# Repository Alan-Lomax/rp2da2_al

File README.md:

# rp2da2

Model Railway Distributed Automation for RP2 (and other MicropPython MCUs).

---

## Hardware and Environment

The primary target Micro Controller Units for this project are Raspberry Pi RP2
based and run MicroPython V1.26 or later. Testing has principly taken place on
Pico, Pico W, Pico 2W and Arduino Nano RP2040 Connect platforms.
DCC and RailCom components use the RP2 Programmable IO peripheral so must be run
on an RP2040 or RP2350 based MCU.
Other application components
may run on other MicroPython capabable platforms with no, or minor modifications.

Primary components are:

- a command station with integrated booster/RailCom cutout and global RailCom detector
- a local RailCom detector module with up to four detectors and current based occupancy detection.

A booster is required to convert the DCC signal into a form suitable for
suppling power directly to track. The reference booster is the Texas
Instruments DRV8874 mounted on a Pololu header. This also acts as the RailCom cutout. This may deliver up to 2.9 A
instantaniously but is only rated for 2.1 A continuous load. You will also
need a suitable DC power supply.

RailCom detectors have been specifically designed for this project with circuit
schematics and PCB designs for both command station and local detectors. The PCB designs
and applications have been designed around a standard set of GPIO pin
allocations. The local RailCom detector also provides a block occupancy indication using
conventional current flow detection. This triggers at a nominal 1 mA enabling detection of 10 kΩ wheel set resistors.
SPI1 and other GPIO pins not currently used by the application suite
may be exposed PCB on headers.

### GPIO Pins, I2C & SPI

On the command station one global detector is
available for the receipt of Channel 2 datagrams. Pin allocations for a Pico based command station are as follows.
Pin allocations on other platforms may differ.

|GPIO Pin (Pico & Nano)|Function|
|---|---|
|4|OLED I2C0:sda|
|5|OLED I2C0:scl|
|16|RailCom Ch 2 rx|
|18|DRV8874 EN|
|19|DRV8874 nSleep|
|20|DRV8874 PH|
|21|DRV8874 nFault|
|22|NeoPixel chain (2 LEDs)|
|26|DRV8874 Current Sense|
|Ground|DRV8874 iMode|
|Ground|DRV8874 pMode|
|NC|DRV8874 Vref|
|22|NeoPixel chain (2 LEDs)|

The following table shows pin allocations for a four block local detector on a Pico series
platform. Pin allocations on other platforms may differ. Other platforms may be able to
support additional local detectors.

I2C0, I2C1 and SPI1 pin assignments follow the MicroPython default pin assignments for
these peripherals.

SPI1 may be wired to a PCB header for off board connection.

I2C1 is used to support conventional current based detector functions.
It may be wired to a PCB header for off board connection too.

|GPIO Pin|Pico / Pico W|
|---|---|
|4|OLED I2C0:sda|
|5|OLED I2C0:scl|
|6|I2C1:sda|
|7|I2C1:scl|
|8|SPI1 MISO|
|9|SPI1 CS(primary)|
|10|SPI1 SCK|
|11|SPI1 MOSI|
|12|SPI1 additional GPIO (e.g. interrupt)|
|13|SPI1 CS(alternative)|
|14|RailCom ch 1 (a) rx|
|15|RailCom ch 1 (a) orientation|
|16|RailCom ch 1 (b) rx|
|17|RailCom ch 1 (b) orientation|
|18|RailCom ch 1 (c) rx|
|19|RailCom ch 1 (c) orientation|
|20|RailCom ch 1 (d) rx|
|21|RailCom ch 1 (d) orientation|
|22|NeoPixel chain (5 LEDs)|
|26|User press button|
|27|RailCom cutout detect|

### Programmable Input/Output & State Machines

The DCC and RailCom components make extensive use of the RP2 Programmable
Input/Output (PIO) peripherals. Each PIO peripheral has four State Machines.
On the Pico W and Pico2 W use of the radio module also requires use of a PIO
State Machine and a State Machine may also be used to drive a NeoPixel chain.
The RP2040 has 2 PIO peripherals and the RP2350 has 3.  MicroPython numbers
the State Machines on these as 0 to 7 and 0 to 11 respectively.

Note that the tables show the default radio state
machines as grabbed if available by the MicroPython
Wi-Fi module/RP SDK library.
The MicroPython application code leaves these
free for the radio rather than specifically
allocating them.

#### Command Station/Global Detector

|State Machine|Function|
|---|---|
|0|DCC generation|
|1 - 3|Not available. DCC generation uses virtually all PIO 0 memory|
|4|Radio on Pico W|
|5|NeoPixel on Pico / Pico W|
|6|RailCom Channel 2 timing|
|7|RailCom Channel 2 RX|
|8|Radio on Pico2 W|
|9|NeoPixel on Pico2 / Pico2 W|

#### Local Detector

|State Machine|Function|
|---|---|
|0|Block A RailCom Channel 1 timing|
|1|Block A RailCom RX|
|2|Block B RailCom Channel 1 timing|
|3|Block B RailCom RX|
|4|Block C RailCom Channel 1 timing|
|5|Block C RailCom RX|
|6|Block D RailCom Channel 1 timing|
|7|Block D RailCom RX|
|8|Radio on Pico2 W|
|9|NeoPixel on Pico2 / Pico2 W|

## Software Modules

### Utility & UI

**device** - This provides the Device class, a base class for hardware device
drivers and similar objects.

**oled0_91** - Module for 0.91 inch OLED on i2c0

**led** - Module to drive ws2812 LEDs or similar.  A string of up to five LEDs is supported.
The first LED displays the backend communications state. Additional LEDs display the
command station track status or local block status as appropriate.

**screen** - This is the screen application module. It specifies the Screen class.

### Communications

**mqtt_client** - This provides a simple MQTT client. Use of MQTT requires an MQTT broker. E.g Mosquitto. There are ports
of this for Windows, MAC/OS, and Linux (e.g. Ubuntu, Raspberry Pi OS).

**mqtt\*** - Other MQTT modules provide interfaces for MQTT devices and agents.
These may be used with JMRI but JMRI MQTT specifications will need to be
changed from the default. Initially we support cabs, power and blocks.
Blocks include occupancy sensor and RailCom reporter.

**wifi** - This acts as wrapper for the standard MicroPython network/Wi-Fi functions.

### DCC and RailCom

These modules are dependent on RP2 series processor programable input/output peripherals (PIO)
for DCC command serialisation and RailCom response processing.

#### Command Station Modules

**dcc_command** - This module provides high level APIs. It and associated modules contain
the functions and classes for DCC command station.

**dcc_cmd_util** - This module contains classes for DCC command objects.

**dcc_cmd_pio** - This module contains the class and functions for low level
DCC Command Serialisation for use with RailCom detection.

**dcc_rc_ch2** - This module contains the functions and classes for DCC RailCom
command station global detector mobile responses on Channel 2.

**trk_mon** - This module monitors the booster and track status by looking at the DRV8874
sleep, enable, fault and current sense pins.

#### Local RailCom Detector Modules

**dcc_rc_ch1** - This module contains the functions and classes for DCC RailCom
block detection on Channel 1.

**blk_mon** - This module contains classes for block occupancy detection based on current
consumption. It works in parallel with the RailCom Channel 1 detector.

#### Common Module

**dcc_rc_pio**  - This module contains the functions and classes for low level
RailCom datagram reading. It's applicable for block occupancy detection on
Channel 1 and central dcc command decoder responses on Channel 2.

---

## Configuration

Configuration files hold information required at runtime.  The files use the JSON format.
They are held in the repository's conf directory. They must be copied to a top level directory on the
target machine called conf. The configuration files in the repository should be taken as examples.
They need to be modified outside the repository to reflect local requirements. The Thonny editor
may be used to update them as required once they have been copied to the target machine.

### Wi-Fi

The config file specifies:

- Network country code
- SSID - your Wi-Fi network name
- password - the network password
- host name - the name to be used by local machine. This needs to be changed
from the MicroPython default to avoid duplicates.

```json
{"country": "myCountry", "password": "myPassword", "ssid": "mySSID", "hostname":"myHostName"}
```

### MQTT

***Pico Configuration***

The config file specifies:

- the MQTT broker's host name
- the local machine client ID.  The client id is required as by default Mosquitto will not permit access without it. However if not specified here the client id will be set to the network host name.
- port - the MQTT port number. By default this is set to 1883 and this setting may be ommitted.

```json
{"broker": "myBroker", "clientId": "myClientName", "port": 1883}
```

On the command station the MQTT connection supports track power and cabs.
On the local detector the MQTT connection supports sensor updates and reporters.
The MQTT connection may be used to communicate with JMRI.
Generally topics match those used by JMRI but some modifications are required to JMRI defaults
as configured on the MQTT connections settings.

***Mosquitto Configuration***

The Mosquitto configuration file is held in mosquitto.conf. The location of the file is OS dependent.
For Raspberry Pi OS it's

```text
/etc/mosquitto/mosquitto.conf
```

A couple of lines may need to be added.

```text
allow_anonymous true

listener 1883
```

Note that connections to Mosquitto will not be authenticated. Do not do this unless inward connections to your network are blocked (or you don't mind aliens hacking your model railway).

***JMRI MQTT Configuration***

  Check 'Additional Connection Settings' under
Preferences->Connections for the MQTT connection to access the JMRI MQTT configuration.

|Setting|Value|
|---|---|
|Sensor send topic:|track/sensor/{0}/set|
|Sensor receive topic:|track/sensor/{0}/event|
|Power send topic:|track/power/set|
|Power receive topic:|track/power/event|

---

## Software Installation

### General

Copy the python (.py) files from the lib and rp2dcc directories to the Pico using Thonny or similar.
Don’t replicate the repository directory structure. Copy the files from both directories to the
lib directory at the Pico files system top level.
Note that MicroPython will only search the top level directory and the lib directory for
*.py files.
Don’t bother with the \_\_init\_\_.py  files.
These are purely documentary at the moment.
Also ignore the test directory.

The screen driver will object if it can’t find the OLED on the i2c bus.
Most 0.91" OLEDs include i2c pull-ups so these should not be needed.

Copy the files from the conf directory to a directory on the Pico named conf.  Edit the configuration files
**after copying**.

### Command Station

The main.py in the examples/command directory is a command station version. It provides MQTT connectivity
allowing the command station to be controlled from JMRI or similar.
Copy this main.py from the command directory to the top level directory on the target device.
Alternatively there is a test harness test_dcccmd.py in the test directory.
This may be run using Thonny. Load this into the Thonny editor window and ‘Run current script’
(green play button). It will auto-detect whether on a RP Pico or
Arduino Nano RP2040 Connect and allocate the detector pins accordingly.
It creates the DCCCommand object (named dcc).

If OK you will get an invitation to type at the REPL, but the program will still be
running in the background. The OLED display shows a ’splash’.

You can enter DCC API commands at the REPL preceded by
'dcc.'. E.g.:

```py
>>> dcc.power(1)
```

### Block Detector

The main.py scripts in the dual\_, and quad\_ local_detect directories are the block detector versions. They
monitor two and four blocks respectively.

They provide MQTT connectivity
allowing the block detector to report to JMRI or similar.
Copy the main.py from the dual or quad directory to the top level directory on the target device.

Alternatively there are test harnesses in the test directory.

***test_dccrc1.py*** runs the local RailCom detectors.

***test_quad_blk.py*** runs the current based occupancy Train detectors.

Both may be run using Thonny. Load the program into the Thonny editor window and ‘Run current script’
(green play button). The program will auto-detect whether on a RP Pico or
Arduino Nano RP2040 Connect and allocate the detector pins accordingly.
It creates the channel 1 block detector objects or current based detector for the blocks.

The program will run forever.

Block occupancy details will be displayed on the OLED screen. Press the user button to see RailCom stats.

---

## DCC API

### Module dcc_command

---
class **DCCCommand** *(DCC_pn, sleep_pn, gen_sm_num, enable_pn)*

Parameters

- *DCC_pn* Pin number allocated for DCC output.

- *sleep_pn* Pin number allocated to the booster for powering the track

- *gen_sm_num* PIO state machine number to be used for DCC Generation

- *enable_pn* Pin number to enable the DRV8874.

---

method **power** *(p=None)*

DCC Power On/Off

Start and stop command packet transmission scheduling.

Changing the power state will cause the new power state available flag to be set.

Parameters

- *p* 1 for power on, 0 for power off, None for get power status

Returns

- power status as held by the DCC generator.

---

method **read_cv** *(address, cv_num)*

This initiates reading a CV using Programming on Main in conjunction with RailCom.
The command is validated and the read request scheduled for action. The addressed decoder must be
active and the command will be rejected by the command generator class this is not true.

The CV value will be displayed on the OLED.

Parameters

- *address*

- *cv_num* cv number as entered - users count from 1, DCC counts from 0!

---

method **write_cv** *(address, cv_num, new_val)*

This initiates writing a CV using Programming on Main in conjunction with RailCom.

The command is validated and the write request scheduled for action. The addressed
decoder must be active and the command will be rejected by the command generator class
this is not true.

The updated CV value will be displayed on the OLED if the write is successful.

Parameters

- *address*

- *cv_num* cv number as entered - users count from 1, DCC counts from 0!

- *new_val* the new value for the CV

---

method **set_fg1** *(address, f_num, state)*

Set Function Group 1

This sets or clears a function in group 1. The forward light is usually function number 0.

See NMRA S-9.2.1 Section 2.3.4

Parameters

- *address* the address of the decoder - may be short or long

- *f_num* function number to set or clear

- *state* 1 for set, 0 for clear

Returns

- True if validation is passed and the packet is scheduled for transmission. False if validation fails.

---

method **set_speed** *(address, dir, speed)*

Set Speed.

This sets the direction and speed. Direction may be forward or reverse.

The packet generated will be for a 128 step speed setting and decoders must be configured for
28/128 speed steps.

See NMRA S-9.2.1 Section 2.3.2.1

Parameters

- *address* the address of the decoder - may be short or long

- *direction* 1 for forward, -1 for reverse

- *speed* the speed to be set - range 0 to 127

Returns

- True if validation is passed and the packet is scheduled for transmission. False if validation fails.

---

method **wait_for_flag** *()*

Wait for the new state available flag.

The new state available flag is an instance of the asyncio.ThreadSafeFlag class
and when set, it indicates that the power state has changed. This method waits
for the flag to be set. When called from another asynchio thread
that thread will wait pending the setting of the flag.
It must be called from a coroutine.

---

Available constants are:

```py
# Forward direction
FWD = const(1)

# Reverse Direction
REV = const(-1)

# Power Off
OFF = const(0)

# Power On
ON = const(1)
```

---

### Module dcc_rc_ch1

---

class **RComBlkDet** *(blk_name, rc_sm_num, rx_pin, led, dcc_pin)*

Parameters

- *blk_name* the name of the block
- *rc_sm_num*  the first state machine number
- *rx_pin* the RailCom local detector rx data pin
- *led* the led number on the led string associated with the block
- *dcc_pin* the RailCom local detector dcc sense pin

---

method **wait_for_flag** *()*

Wait for the new block state available flag.

The new state available flag is an instance of the asyncio.ThreadSafeFlag class
and when set, it indicates that the block detection state state has changed.
This method waits for the flag to be set. When called from another asynchio thread
that thread will wait pending the setting of the flag.
It must be called from a coroutine.

---

method **get_block_state** *()*

Get the current block state

This returns the current block state. The block state is a tuple of the block
status and any RailCom information available. The block status may be:

- *Device.UNKNOWN* the block state is unknown
- *Device.BLK_CH1* RailCom Channel 1 information has changed.

RailCom information, if available, is a tuple:

- *address type* 's', 'l' or 'c' for short, long or consist
- *address* as an integer number
- *orientation* 1 or -1

---

method **get_error_counts** *()*

Get Error Counts

Counts of errors are kept. Broadly errors are communication errors or content errors. Content errors
may be caused by faulty decoders, but typically are the result of undetected communicaton errors.

Communication errors are:

- Overrun error (missing stop bit)
- Hamming Weighting high or low (not 4)

See code for other errors.

---

method **get_cb_count** *()*

Get Read Count

The number of calls to the read routine. I.e the number of times
that data has been received during a channel 1 window.

---

method **reset_stats** *()*

Reset Statistics

Reset error counts etc.

---

### DCC Diagnostics

---

function **print_stats** *(reset = True)*

This prints diagnostic information on DCC commands
and RailCom. By default the diagnostics are cleared after being printed.
Available in both test_dcccmd and test_dccrc1 modules. Press the user button
to run this from the test_dccrc1 module.

---

function **print_dyn_info** *()*

This prints dynamic information received from
decoders (datagram id 7).
Available in test_dcccmd module.

---

## Commissioning PCBs

### Module test_lcl_bd

This is a free standing module for assisting in commissioning the 4 way local detector board.
It's available in the repository test directory.
It is run directly from Thonny and is not installed on the Pico.

It's useage is covered in the commisioning script.

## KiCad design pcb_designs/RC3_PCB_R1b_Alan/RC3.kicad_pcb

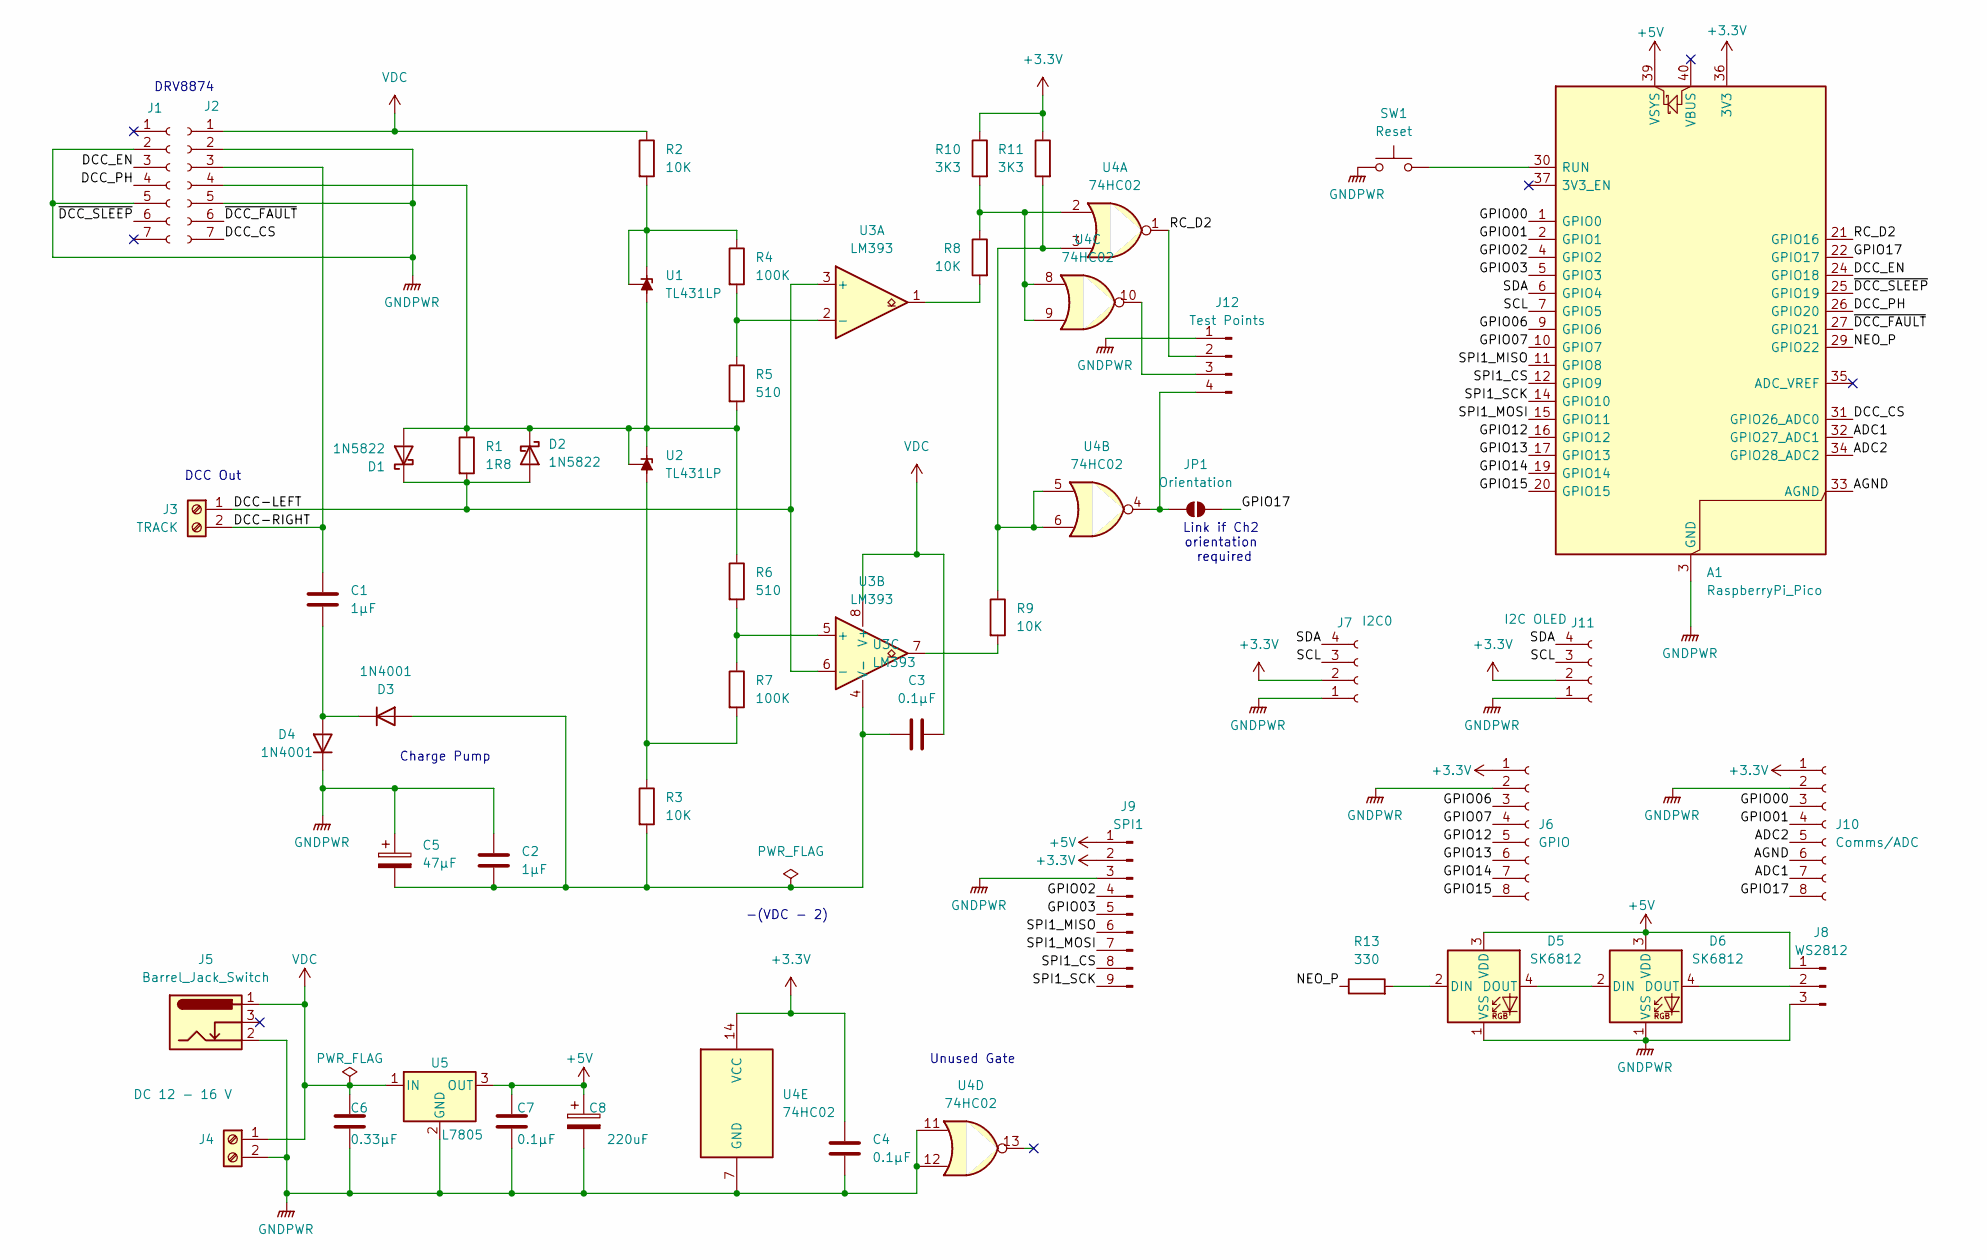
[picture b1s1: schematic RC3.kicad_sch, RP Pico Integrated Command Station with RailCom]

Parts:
A1: RaspberryPi_Pico; RaspberryPi_Pico_Common_THT
C1, C2: 1µF; C_Disc_D7.0mm_W2.5mm_P5.00mm
C3, C4, C7: 0.1µF; C_Disc_D7.0mm_W2.5mm_P5.00mm
C5: 47µF; CP_Radial_D5.0mm_P2.00mm
C6: 0.33µF; C_Disc_D7.0mm_W2.5mm_P5.00mm
C8: 220uF; CP_Radial_D6.3mm_P2.50mm
D1, D2: 1N5822; D_DO-201AD_P15.24mm_Horizontal
D3, D4: 1N4001; D_DO-41_SOD81_P10.16mm_Horizontal
D5, D6: SK6812; LED_SK6812_PLCC4_5.0x5.0mm_P3.2mm
J1, J2: Conn_01x07_Socket; PinSocket_1x07_P2.54mm_Vertical
J3: TRACK; TerminalBlock_bornier-2_P5.08mm
J4: DC 12 - 16 V; TerminalBlock_bornier-2_P5.08mm
J5: Barrel_Jack_Switch; BarrelJack_CUI_PJ-102AH_Horizontal
J6: GPIO; PinSocket_1x08_P2.54mm_Vertical
J7: I2C0; PinSocket_1x04_P2.54mm_Vertical
J8: WS2812; PinHeader_1x03_P2.54mm_Vertical
J9: SPI1; PinHeader_1x09_P2.54mm_Vertical
J10: Comms/ADC; PinSocket_1x08_P2.54mm_Vertical
J11: I2C OLED; SSD1306-0.91-OLED-4pin-128x32
J12: Test Points; PinHeader_1x04_P2.54mm_Vertical
JP1: Orientation; SolderJumper-2_P1.3mm_Open_RoundedPad1.0x1.5mm
R1: 1R8; R_Axial_DIN0516_L15.5mm_D5.0mm_P20.32mm_Horizontal
R2, R3, R8, R9: 10K; R_Axial_DIN0207_L6.3mm_D2.5mm_P7.62mm_Horizontal
R4, R7: 100K; R_Axial_DIN0207_L6.3mm_D2.5mm_P7.62mm_Horizontal
R5, R6: 510; R_Axial_DIN0207_L6.3mm_D2.5mm_P7.62mm_Horizontal
R10, R11: 3K3; R_Axial_DIN0207_L6.3mm_D2.5mm_P7.62mm_Horizontal
R13: 330; R_Axial_DIN0207_L6.3mm_D2.5mm_P7.62mm_Horizontal
SW1: Reset; SW_TH_Tactile_Omron_B3F-10xx
U1, U2: TL431LP; TO-92_Inline
U3: LM393; DIP-8_W7.62mm
U4: 74HC02; DIP-14_W7.62mm
U5: L7805; TO-220-3_Vertical

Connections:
+3.3V: A1.36 (3V3), C4.1, J6.1, J7.2, J9.2, J10.1, J11.2, R10.1, R11.1, U4.14 (VCC)
+5V: A1.39 (VSYS), C7.1, C8.1, D5.3 (VDD), D6.3 (VDD), J8.1, J9.1, U5.3 (OUT)
/ADC1: A1.32 (GPIO27_ADC1), J10.7
/ADC2: A1.34 (GPIO28_ADC2), J10.5
/AGND: A1.33 (AGND), J10.6
/DCC-LEFT: D1.1 (K), D2.2 (A), J3.1, R1.2, U3.3 (+), U3.6 (-)
/DCC-RIGHT: C1.1, J2.3, J3.2
/DCC_CS: A1.31 (GPIO26_ADC0), J2.7
/DCC_EN: A1.24 (GPIO18), J1.3
/DCC_PH: A1.26 (GPIO20), J1.4
/GPIO00: A1.1 (GPIO0), J10.3
/GPIO01: A1.2 (GPIO1), J10.4
/GPIO02: A1.4 (GPIO2), J9.4
/GPIO03: A1.5 (GPIO3), J9.5
/GPIO06: A1.9 (GPIO6), J6.3
/GPIO07: A1.10 (GPIO7), J6.4
/GPIO12: A1.16 (GPIO12), J6.5
/GPIO13: A1.17 (GPIO13), J6.6
/GPIO14: A1.19 (GPIO14), J6.7
/GPIO15: A1.20 (GPIO15), J6.8
/GPIO17: A1.22 (GPIO17), J10.8, JP1.2 (B)
/NEO_P: A1.29 (GPIO22), R13.1
/RC_D2: A1.21 (GPIO16), J12.2, U4.1
/SCL: A1.7 (GPIO5), J7.3, J11.3
/SDA: A1.6 (GPIO4), J7.4, J11.4
/SPI1_CS: A1.12 (GPIO9), J9.8
/SPI1_MISO: A1.11 (GPIO8), J9.6
/SPI1_MOSI: A1.15 (GPIO11), J9.7
/SPI1_SCK: A1.14 (GPIO10), J9.9
/~DCC_FAULT: A1.27 (GPIO21), J2.6
/~DCC_SLEEP: A1.25 (GPIO19), J1.6
GNDPWR: A1.3 (GND), A1.8 (GND), A1.13 (GND), A1.18 (GND), A1.23 (GND), A1.28 (GND), A1.38 (GND), C2.1, C4.2, C5.1, C6.2, C7.2, C8.2, D4.1 (K), D5.1 (VSS), D6.1 (VSS), J1.2, J1.5, J2.2, J2.5, J4.2, J5.2, J6.2, J7.1, J8.3, J9.3, J10.2, J11.1, J12.1, SW1.1, U4.7 (GND), U4.11, U4.12, U5.2 (GND)
unnamed: A1.30 (RUN), SW1.2
unnamed: D1.2 (A), D2.1 (K), J2.4, R1.1, R5.2, R6.1, U1.2 (A), U2.1 (REF), U2.3 (K)
unnamed: C2.2, C3.2, C5.2, D3.2 (A), R3.2, U3.4 (V-)
unnamed: C1.2, D3.1 (K), D4.2 (A)
unnamed: D5.2 (DIN), R13.2
unnamed: D5.4 (DOUT), D6.2 (DIN)
unnamed: D6.4 (DOUT), J8.2
unnamed: J12.3, U4.10
unnamed: J12.4, JP1.1 (A), U4.4
unnamed: R8.2, U3.1
unnamed: R9.2, U3.7
unnamed: R8.1, R10.2, U4.2, U4.8, U4.9
unnamed: R9.1, R11.2, U4.3, U4.5, U4.6
unnamed: R2.2, R4.1, U1.1 (REF), U1.3 (K)
unnamed: R3.1, R7.2, U2.2 (A)
unnamed: R4.2, R5.1, U3.2 (-)
unnamed: R6.2, R7.1, U3.5 (+)
VDC: C3.1, C6.1, J2.1, J4.1, J5.1, R2.1, U3.8 (V+), U5.1 (IN)

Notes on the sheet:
Charge Pump
Link if Ch2 orientation required
DCC Out
-(VDC - 2)
DRV8874
Unused Gate

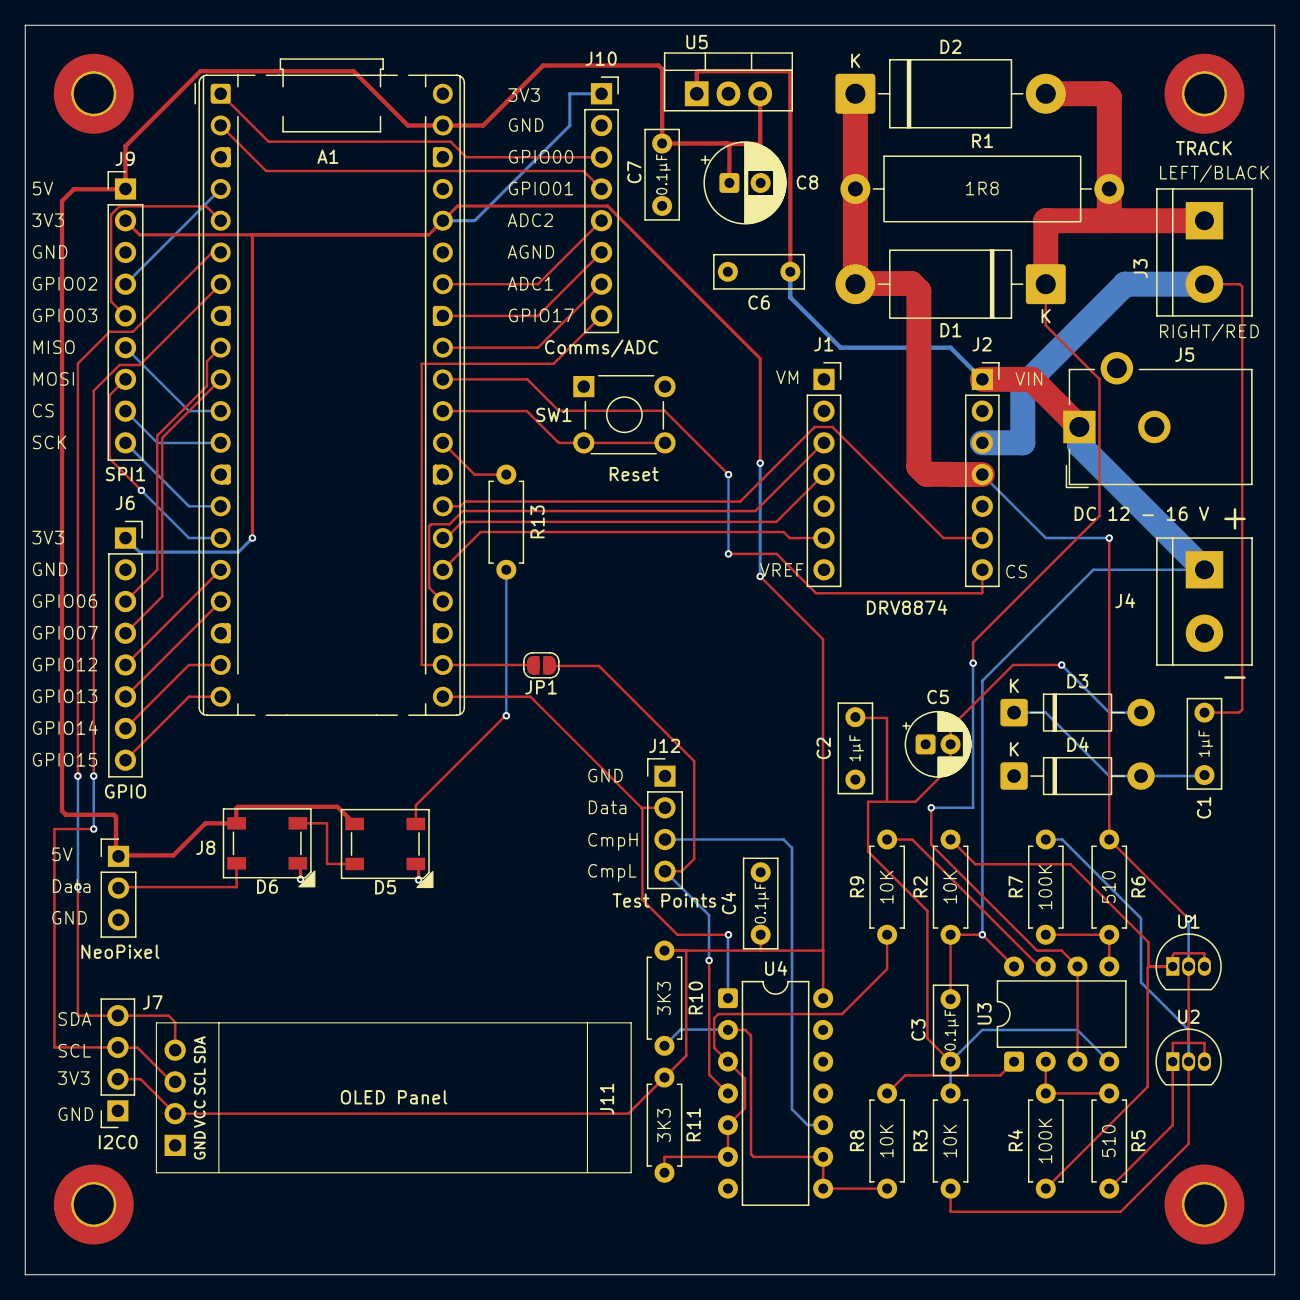
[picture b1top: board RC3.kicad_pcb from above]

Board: 2 copper layers, 100.0 x 100.0 mm, 50 parts (0 on the bottom side), 50 nets.

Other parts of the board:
H1, H2, H3, H4: MountingHole; MountingHole_3.2mm_M3_Pad_TopBottom

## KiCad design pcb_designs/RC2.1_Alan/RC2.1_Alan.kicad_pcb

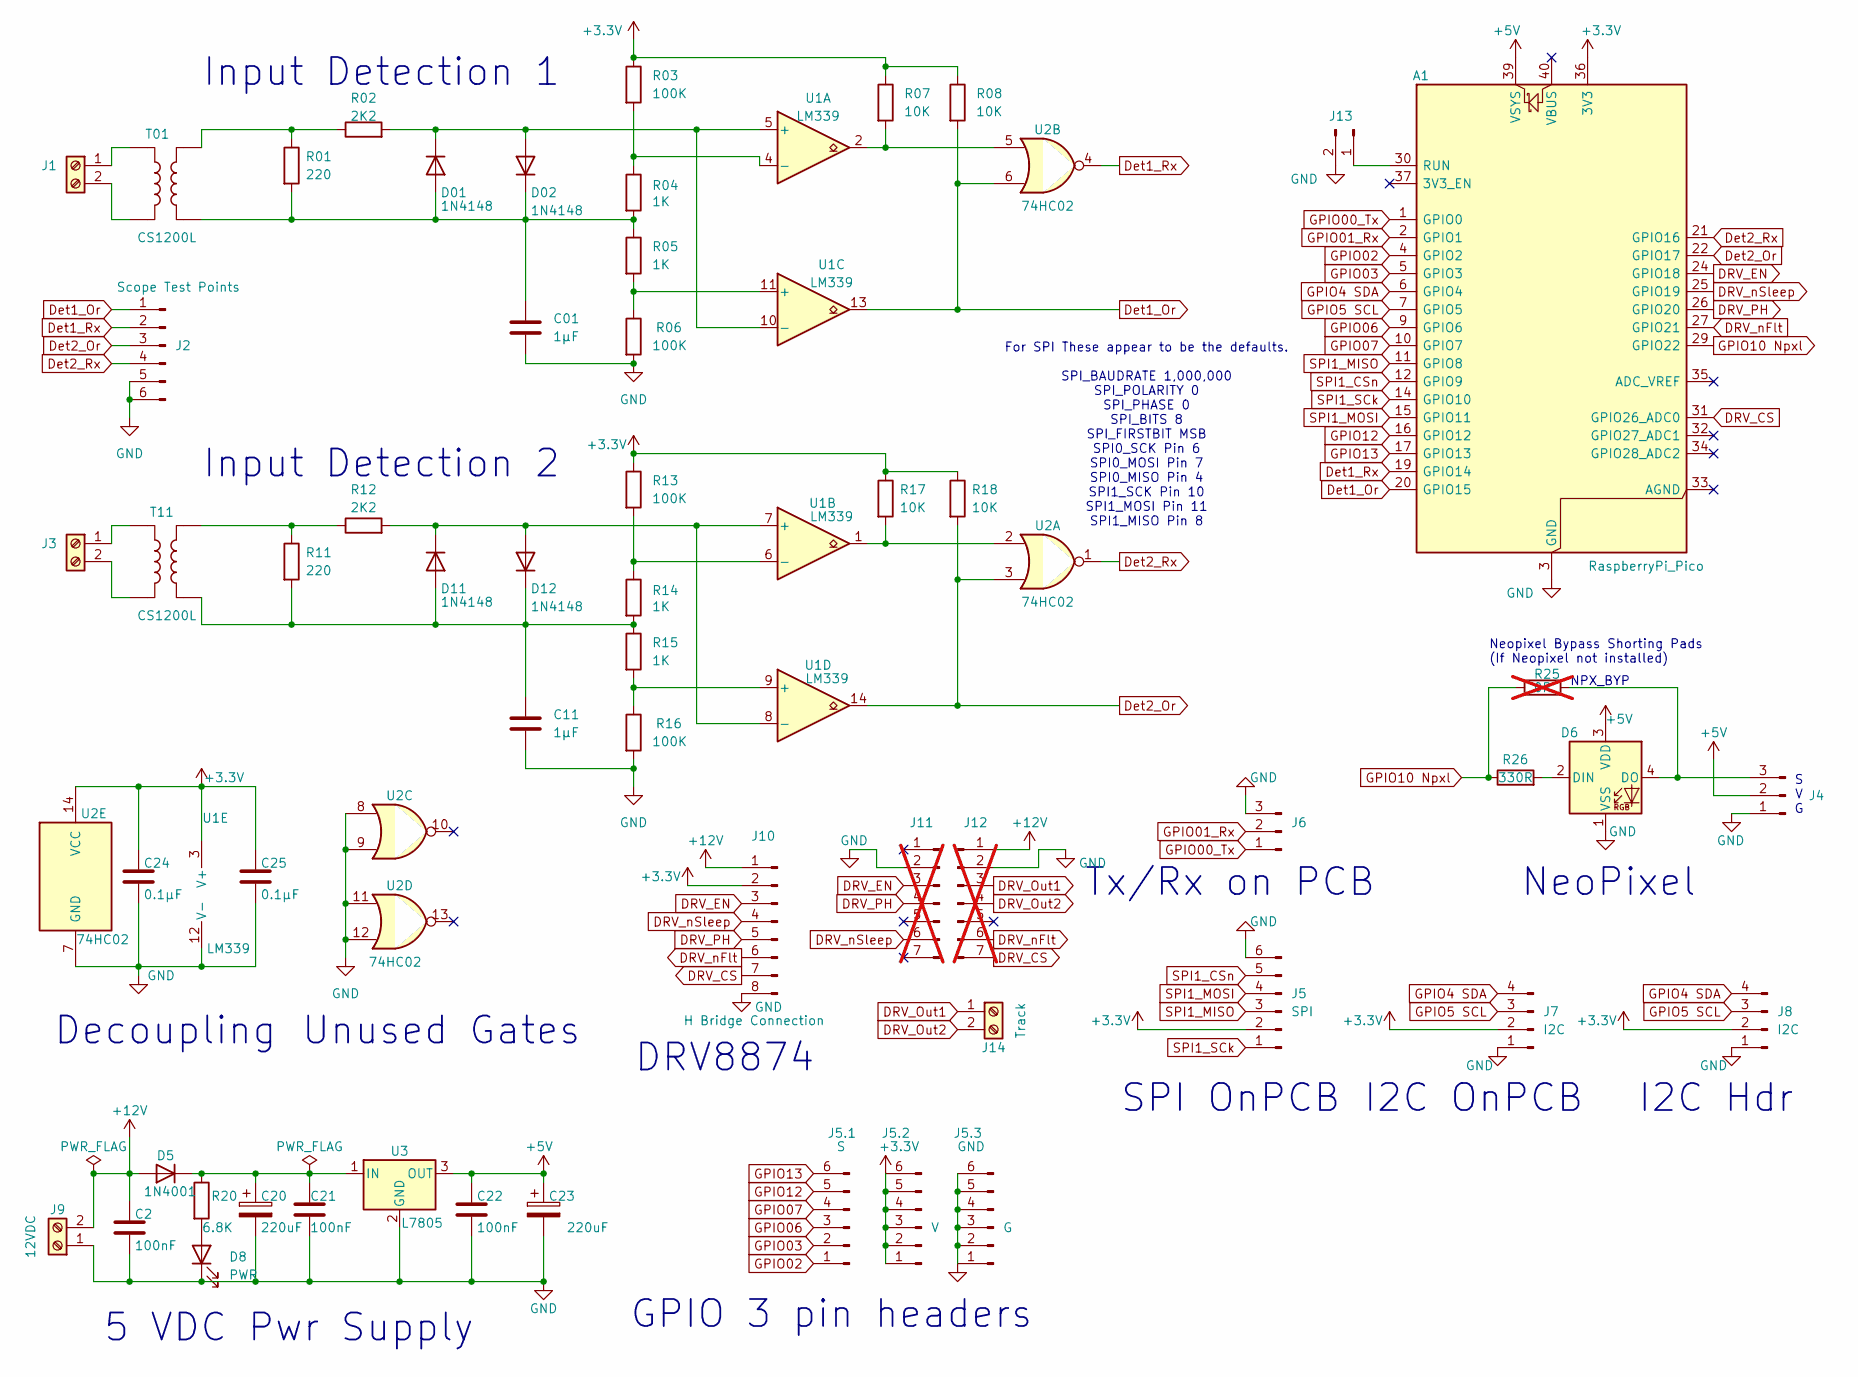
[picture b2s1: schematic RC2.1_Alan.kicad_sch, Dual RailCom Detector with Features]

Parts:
A1: RaspberryPi_Pico; RaspberryPi_Pico_Common_Unspecified
C01, C11: 1µF; C_Disc_D7.0mm_W2.5mm_P5.00mm
C2, C21, C22: 100nF; C_Disc_D7.0mm_W2.5mm_P5.00mm
C20, C23: 220uF; CP_Radial_D6.3mm_P2.50mm
C24, C25: 0.1µF; C_Disc_D7.0mm_W2.5mm_P5.00mm
D01, D02, D11, D12: 1N4148; D_DO-35_SOD27_P7.62mm_Horizontal
D5: 1N4001; D_DO-41_SOD81_P10.16mm_Horizontal
D6: Inolux_IN-PI554FCH; LED_Inolux_IN-PI554FCH_PLCC4_5.0x5.0mm_P3.2mm
D8: PWR; LED_D5.0mm
J1, J3: Screw_Terminal_01x02; TerminalBlock_bornier-2_P5.08mm
J2: Scope Test Points; Molex_KK-254_AE-6410-06A_1x06_P2.54mm_Vertical
J4: Npx; PinHeader_1x03_P2.54mm_Vertical
J5: SPI; PinHeader_2x03_P2.54mm_Vertical
J5.1: S; PinHeader_1x06_P2.54mm_Vertical
J5.2: V; PinHeader_1x06_P2.54mm_Vertical
J5.3: G; PinHeader_1x06_P2.54mm_Vertical
J6: Tx/Rx; PinHeader_1x03_P2.54mm_Vertical
J7: I2C; SSD1306-0.91-OLED-4pin-128x32
J8: I2C; PinHeader_1x04_P2.54mm_Vertical
J9: 12VDC; TerminalBlock_Phoenix_MKDS-3-2-5.08_1x02_P5.08mm_Horizontal
J10: H Bridge Connection; PinHeader_1x08_P2.54mm_Vertical
J11, J12: Conn_01x07_Pin; PinHeader_1x07_P2.54mm_Vertical; not fitted
J13: Reset; PinHeader_1x02_P2.54mm_Vertical
J14: Track; TerminalBlock_Phoenix_MKDS-3-2-5.08_1x02_P5.08mm_Horizontal
R01, R11: 220; R_Axial_DIN0207_L6.3mm_D2.5mm_P7.62mm_Horizontal
R02, R12: 2K2; R_Axial_DIN0207_L6.3mm_D2.5mm_P7.62mm_Horizontal
R03, R06, R13, R16: 100K; R_Axial_DIN0207_L6.3mm_D2.5mm_P7.62mm_Horizontal
R04, R05, R14, R15: 1K; R_Axial_DIN0207_L6.3mm_D2.5mm_P7.62mm_Horizontal
R07, R08, R17, R18: 10K; R_Axial_DIN0207_L6.3mm_D2.5mm_P7.62mm_Horizontal
R20: 6.8K; R_Axial_DIN0207_L6.3mm_D2.5mm_P7.62mm_Horizontal
R25: 0R; R_1020_2550Metric_Pad1.33x5.20mm_HandSolder; not fitted
R26: 330R; R_Axial_DIN0207_L6.3mm_D2.5mm_P7.62mm_Horizontal
T01, T11: CS1200L; Transformer_THT_MERG_DTC; Manufacturer_Part_Number CS1200L; Mouser Part Number 994-CS1200L
U1: LM339; DIP-14_W7.62mm
U2: 74HC02; DIP-14_W7.62mm
U3: L7805; TO-220-3_Vertical

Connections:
+3.3V: A1.36 (3V3), C24.1, C25.1, J5.2, J5.2.1, J5.2.2, J5.2.3, J5.2.4, J5.2.5, J5.2.6, J7.2, J8.2, J10.2, R03.1, R07.1, R08.1, R13.1, R17.1, R18.1, U1.3 (V+), U2.14 (VCC)
+5V: A1.39 (VSYS), C22.1, C23.1, D6.3 (VDD), J4.2, U3.3 (OUT)
+12V: C2.1, D5.2 (A), J9.2, J10.1, J12.1
DRV_CS: A1.31 (GPIO26_ADC0), J10.7, J12.7
DRV_EN: A1.24 (GPIO18), J10.3, J11.3
DRV_Out1: J12.3, J14.1
DRV_Out2: J12.4, J14.2
DRV_PH: A1.26 (GPIO20), J10.5, J11.4
DRV_nFlt: A1.27 (GPIO21), J10.6, J12.6
DRV_nSleep: A1.25 (GPIO19), J10.4, J11.6
Det1_Or: A1.20 (GPIO15), J2.1, R08.2, U1.13, U2.6
Det1_Rx: A1.19 (GPIO14), J2.2, U2.4
Det2_Or: A1.22 (GPIO17), J2.3, R18.2, U1.14, U2.3
Det2_Rx: A1.21 (GPIO16), J2.4, U2.1
GND: A1.3 (GND), A1.8 (GND), A1.13 (GND), A1.18 (GND), A1.23 (GND), A1.28 (GND), A1.38 (GND), C01.2, C2.2, C11.2, C20.2, C21.2, C22.2, C23.2, C24.2, C25.2, D6.1 (VSS), D8.1 (K), J2.5, J2.6, J4.1, J5.6, J5.3.1, J5.3.2, J5.3.3, J5.3.4, J5.3.5, J5.3.6, J6.3, J7.1, J8.1, J9.1, J10.8, J11.2, J12.2, J13.2, R06.2, R16.2, U1.12 (V-), U2.7 (GND), U2.8, U2.9, U2.11, U2.12, U3.2 (GND)
GPIO00_Tx: A1.1 (GPIO0), J6.1
GPIO01_Rx: A1.2 (GPIO1), J6.2
GPIO02: A1.4 (GPIO2), J5.1.1
GPIO03: A1.5 (GPIO3), J5.1.2
GPIO4 SDA: A1.6 (GPIO4), J7.4, J8.4
GPIO5 SCL: A1.7 (GPIO5), J7.3, J8.3
GPIO06: A1.9 (GPIO6), J5.1.3
GPIO07: A1.10 (GPIO7), J5.1.4
GPIO10 Npxl: A1.29 (GPIO22), R25.1, R26.1
GPIO12: A1.16 (GPIO12), J5.1.5
GPIO13: A1.17 (GPIO13), J5.1.6
unnamed: A1.30 (RUN), J13.1
unnamed: C01.1, D01.2 (A), D02.1 (K), R01.2, R04.2, R05.1, T01.3
unnamed: D01.1 (K), D02.2 (A), R02.2, U1.5 (+), U1.10 (-)
unnamed: C20.1, C21.1, D5.1 (K), R20.1, U3.1 (IN)
unnamed: D6.2 (DIN), R26.2
unnamed: D6.4 (DO), J4.3, R25.2
unnamed: D8.2 (A), R20.2
unnamed: C11.1, D11.2 (A), D12.1 (K), R11.2, R14.2, R15.1, T11.3
unnamed: D11.1 (K), D12.2 (A), R12.2, U1.7 (+), U1.8 (-)
unnamed: J1.1, T01.6
unnamed: J1.2, T01.4
unnamed: J3.1, T11.6
unnamed: J3.2, T11.4
unnamed: R01.1, R02.1, T01.1
unnamed: R07.2, U1.2, U2.5
unnamed: R11.1, R12.1, T11.1
unnamed: R17.2, U1.1, U2.2
unnamed: R03.2, R04.1, U1.4 (-)
unnamed: R13.2, R14.1, U1.6 (-)
unnamed: R05.2, R06.1, U1.11 (+)
unnamed: R15.2, R16.1, U1.9 (+)
SPI1_CSn: A1.12 (GPIO9), J5.5
SPI1_MISO: A1.11 (GPIO8), J5.3
SPI1_MOSI: A1.15 (GPIO11), J5.4
SPI1_SCk: A1.14 (GPIO10), J5.1

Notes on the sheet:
Unused Gates
DRV8874
Input Detection 2
GPIO 3 pin headers
NPX_BYP
I2C OnPCB
Input Detection 1
S V G
Tx/Rx on PCB
For SPI These appear to be the defaults. SPI_BAUDRATE 1,000,000 SPI_POLARITY 0 SPI_PHASE 0 SPI_BITS 8 SPI_FIRSTBIT MSB SPI0_SCK Pin 6 SPI0_MOSI Pin 7 SPI0_MISO Pin 4 SPI1_SCK Pin 10 SPI1_MOSI Pin 11 SPI1_MISO Pin 8
NeoPixel
5 VDC Pwr Supply
Decoupling
SPI OnPCB
I2C Hdr
Neopixel Bypass Shorting Pads (If Neopixel not installed)

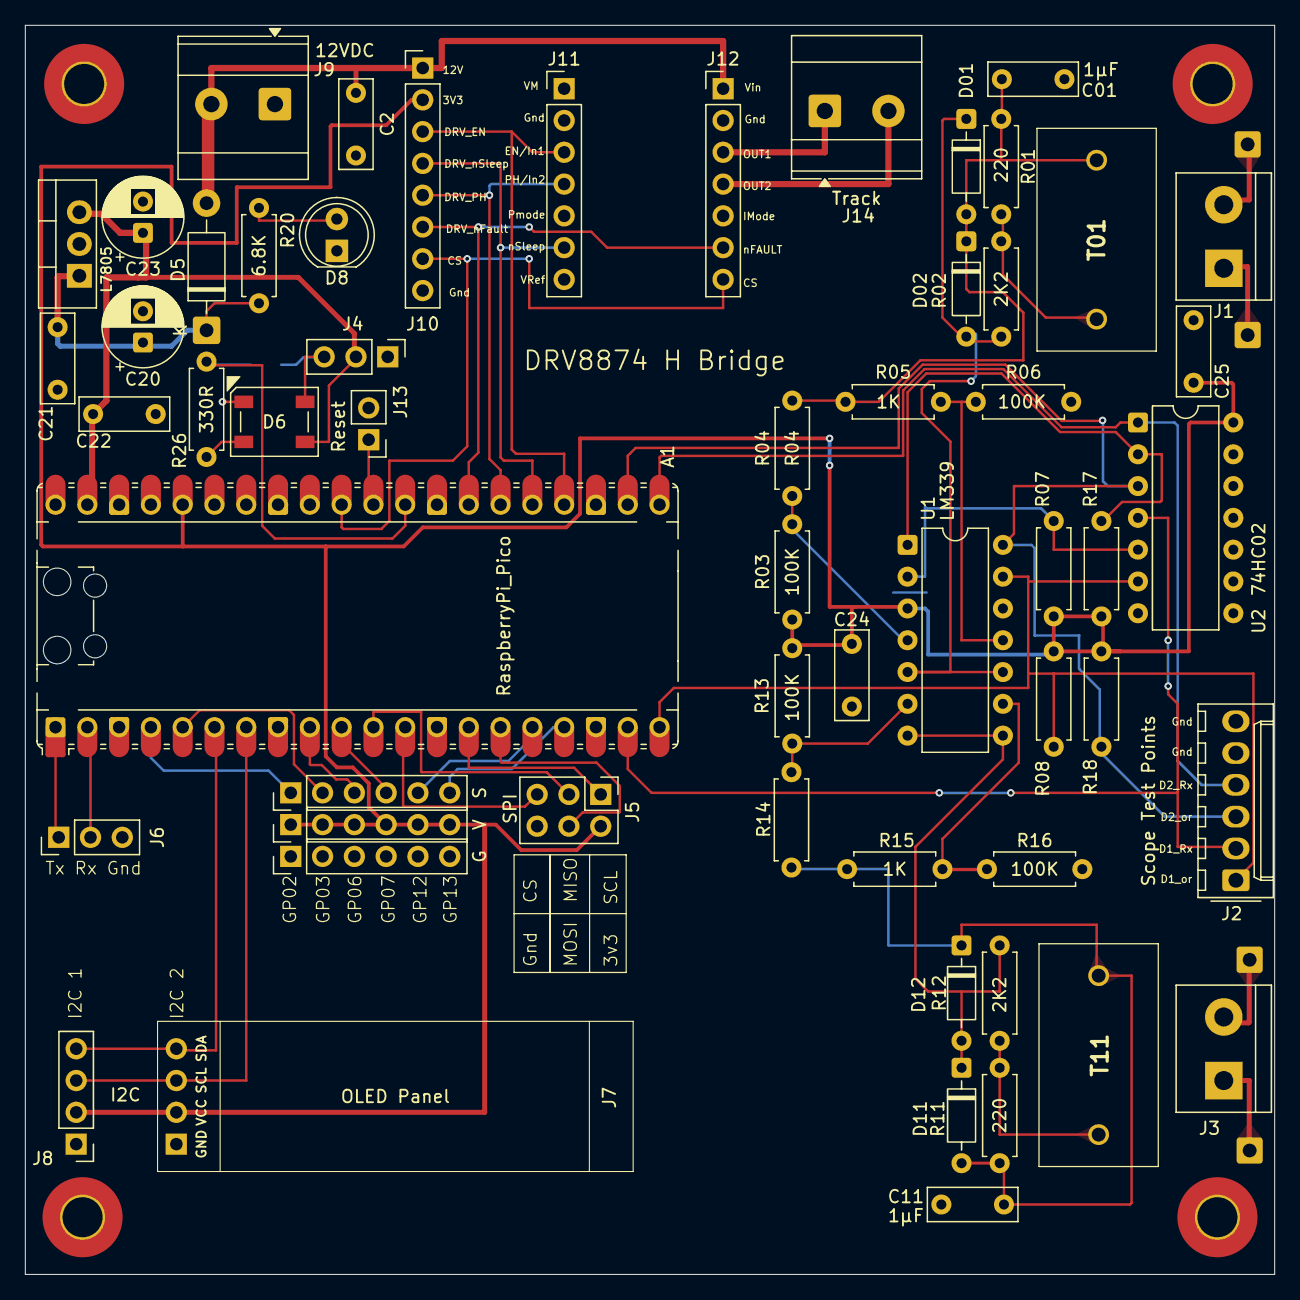
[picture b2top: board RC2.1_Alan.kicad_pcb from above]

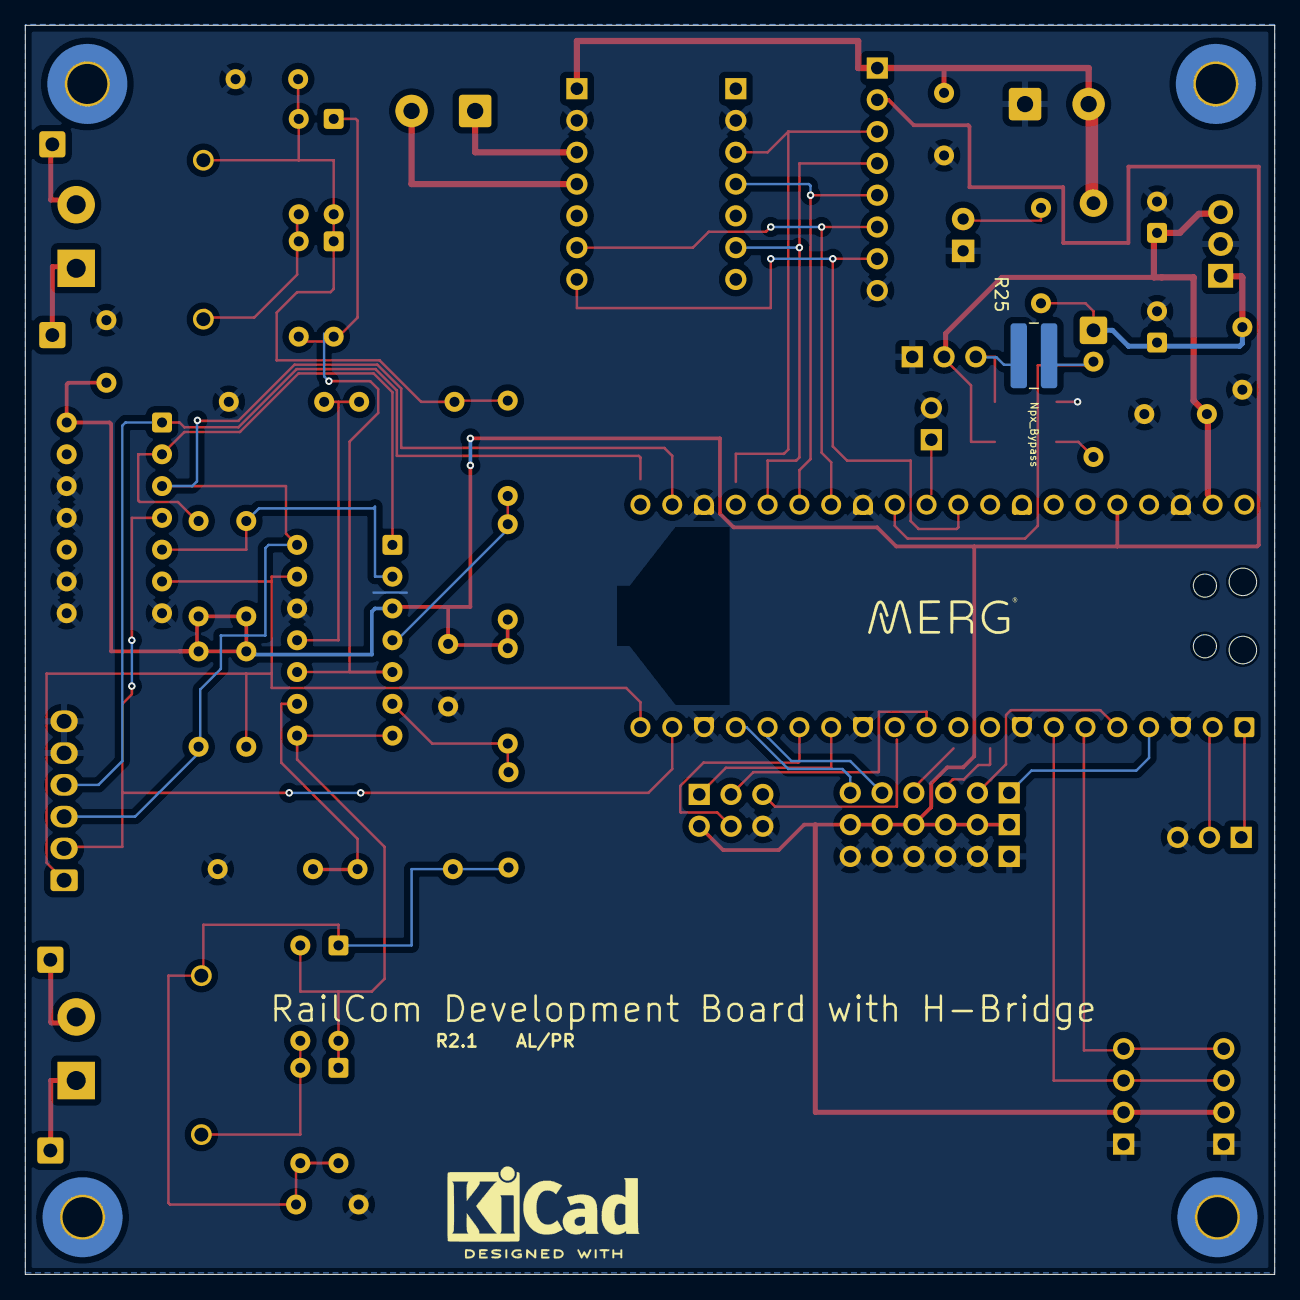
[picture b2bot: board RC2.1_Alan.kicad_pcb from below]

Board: 2 copper layers, 99.8 x 99.8 mm, 59 parts (2 on the bottom side), 51 nets.

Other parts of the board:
MERG: LOGO; New_MERG_Logo 12mm

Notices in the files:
pcb_designs/RC2/RC2.kicad_pcb:
(c) 2025 PR
